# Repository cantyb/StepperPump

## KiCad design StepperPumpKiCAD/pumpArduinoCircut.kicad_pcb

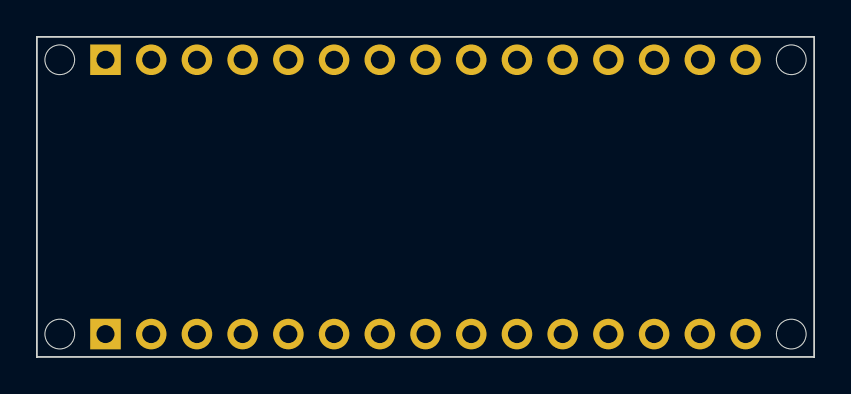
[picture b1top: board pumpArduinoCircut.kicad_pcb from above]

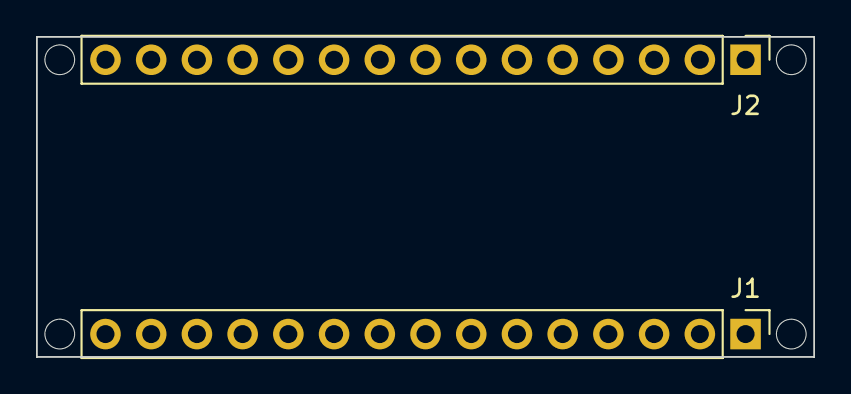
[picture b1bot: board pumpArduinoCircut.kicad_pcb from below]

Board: 2 copper layers, 43.2 x 17.8 mm, 6 parts (2 on the bottom side), 2 nets, no tracks yet.

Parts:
J1: Analog; PinHeader_1x15_P2.54mm_Vertical
J2: Digital; PinHeader_1x15_P2.54mm_Vertical
MH1, MH2, MH3, MH4: MountingHole_65mil

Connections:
/~RESET: J1.13, J2.13
GND: J1.14, J2.12

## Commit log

2023-07-13 Add files via upload
    initial commit
